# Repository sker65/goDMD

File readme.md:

# goDMD

Firmware for den pinguino micro zum bau einer goDmd Uhr.

Blog mit Anleitungen und vielen weiter führenden Hinweisen auf http://go-dmd.de/

# Setup der IDE

Als IDE kann Eclipse IDE genutzt werden. Siehe http://cogito-ergo-blog.de/blog/2015/02/25/eclipse-cdt-zur-pic-pic32-entwicklung-nutzen/

# Setup der Umgebung

Dieses Projekt nutzt einen chipKit core und einige Bibliotheken daraus. Um einen passende Core als libCore_api.a zum Linken zu haben, 
empfielt es sich dafür ebenfalls ein Eclipse CDT Projekt zu machen.
Auf dieses Projekt kann dann verwiesen werden.

## Libraries

Die Libraries die genutzt werden sind direkt aus dem Eclipse Workspace heraus verlinkt und 
zeigen auf die UECIDE Installation im home verzeichnis, wo der chipKit core Quellcode abgelegt ist.
Hier sind ggf. die Pfade in den Eclipse-Links anzupassen.

## IRremote Library
Die IR Remote Library wurde für den _Empfang_ an die PIC Umgebung angepasst und das Recorden
des IR Eingangs im Interrput angepasst.

Was nicht geht ist das Senden von IR Command. Die betreffen Stellen, die die PWM Signale 
erzeugen müssen noch von Arduino nach PIC portiert werden.

# SD Library
Diese Library ist eine projekt lokale Kopie der Lib aus dem ChipKIT core mit kleineren 
Anpassungen, damit sie aus dem pinguino micro ohne Probleme läuft.

Änderungen:
SD:
- seekCur eingefügt.

Sd2Card:
- setTranfersize to 8 bit
- setSpeed to 10000000UL (instead of 20000000UL) faster speed does not work

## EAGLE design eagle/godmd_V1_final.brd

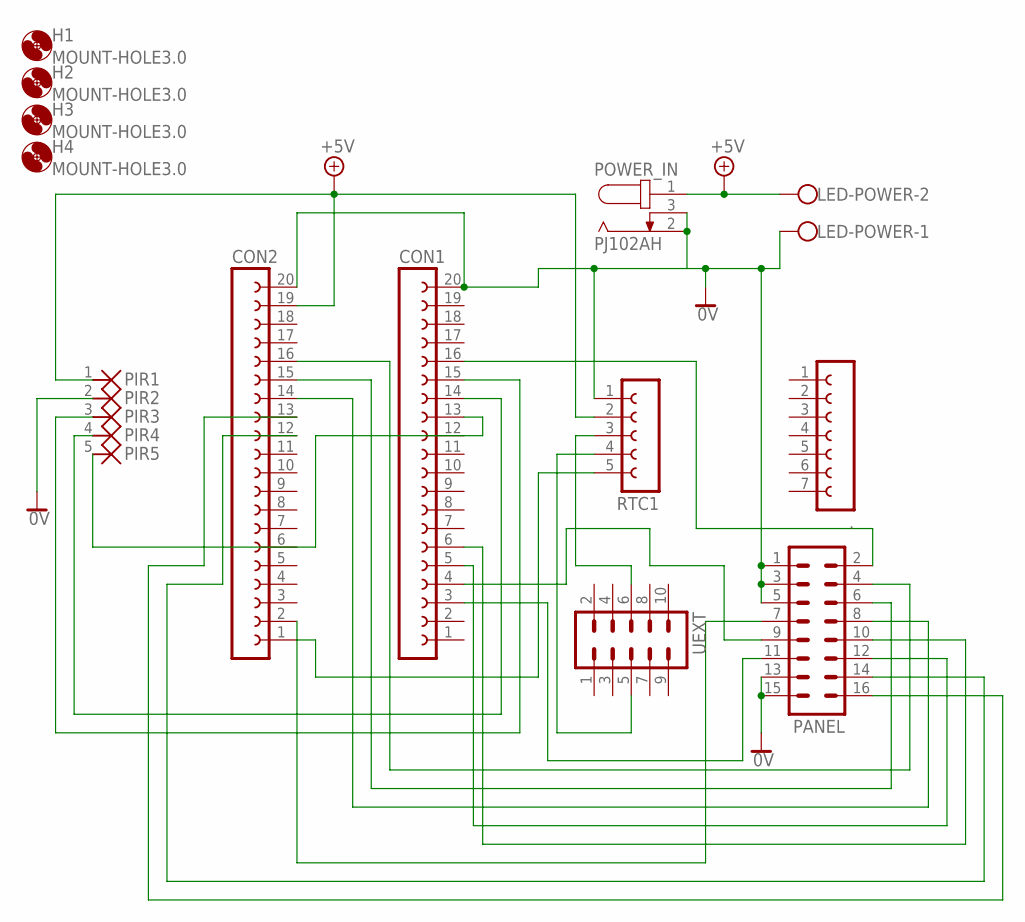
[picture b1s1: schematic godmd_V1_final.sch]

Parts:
.: FE07-1; FE07
CON1, CON2: FE20-1; FE20
H1, H2, H3, H4: MOUNT-HOLE3.0; 3,0
LED-POWER: W237-102
PANEL: MA08-2
PIR: PS25_5
POWER_IN: PJ102AH; PJ102
RTC1: FE05-1
UEXT: ML10

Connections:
0V: CON1.20, CON2.20, LED-POWER.1, PANEL.1, PANEL.3, PANEL.5, PANEL.13, PANEL.15, PIR.2, POWER_IN.2 (1), POWER_IN.3 (2), RTC1.1
+5V: CON2.19, LED-POWER.2, PIR.1, POWER_IN.1 (3), RTC1.2
A: CON1.16, PANEL.2
B: CON2.16, PANEL.4
C: CON2.15, PANEL.6
CLK: CON2.13, PANEL.16
D: CON2.14, PANEL.8
GD1: CON1.6, PANEL.10
GD2: CON1.5, PANEL.12
IRREC: CON1.14, PIR.4
LAT: CON2.12, PANEL.14
unnamed: RTC1.3, UEXT.6
unnamed: RTC1.4, UEXT.5
unnamed: CON2.1, RTC1.5
unnamed: CON2.2, PANEL.7
PIR-AUX: CON1.13, PIR.5
PIRDATA: CON1.15, PIR.3
RD1: CON1.4, PANEL.9
RD2: CON1.3, PANEL.11

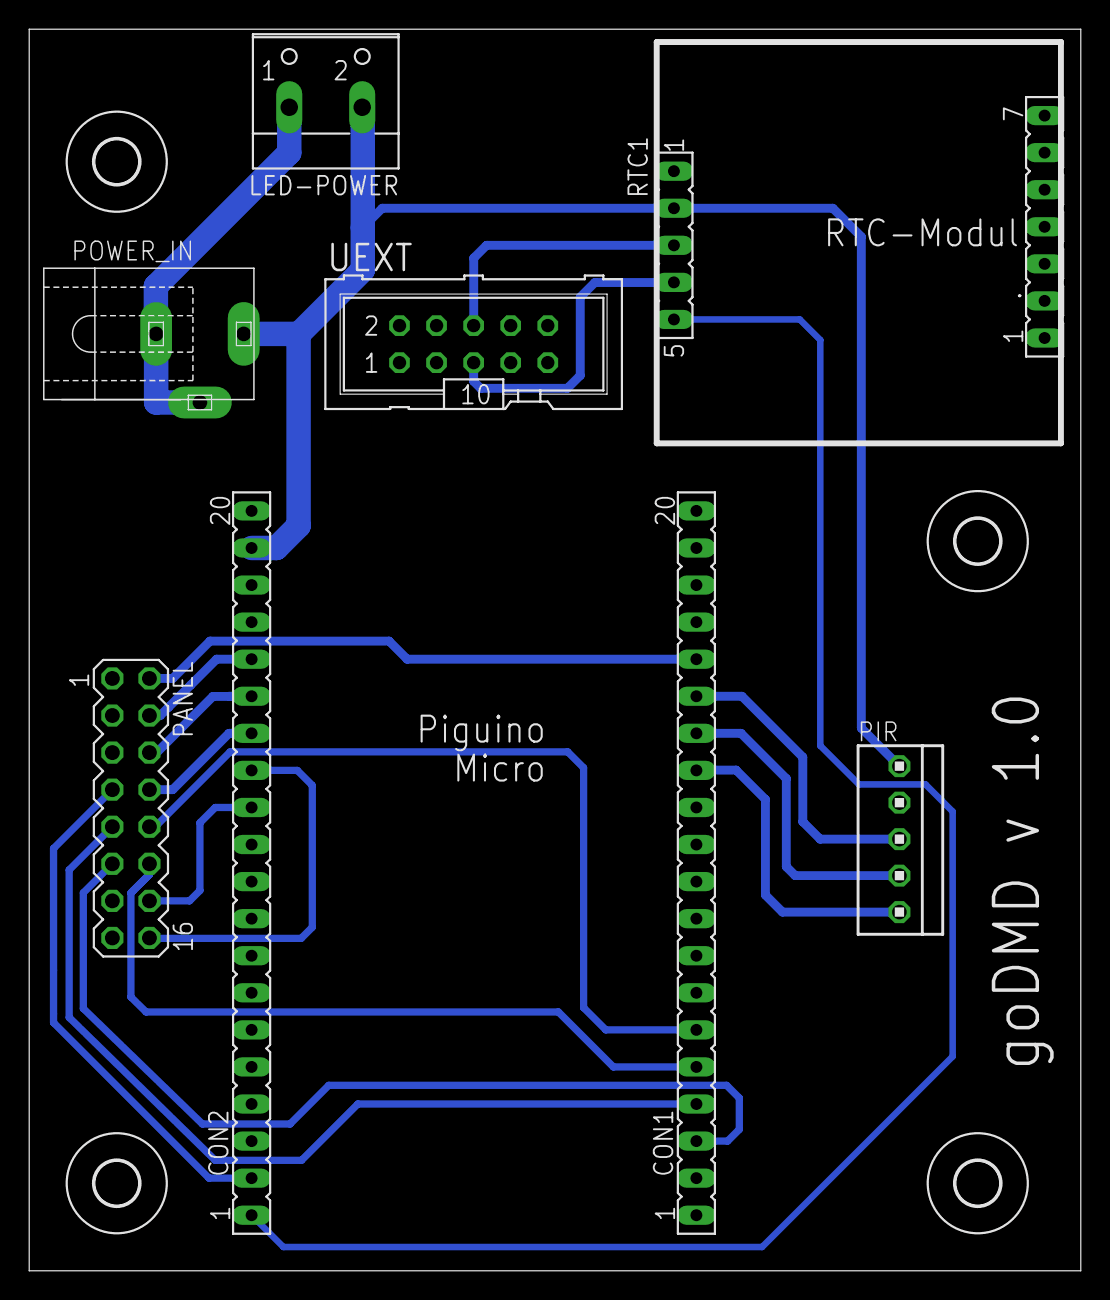
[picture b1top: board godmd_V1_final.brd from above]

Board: 2 copper layers, 72.1 x 85.1 mm, 13 parts (0 on the bottom side), 19 nets.

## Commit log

2015-02-27 first
2015-03-03 - switch to eclipse
2015-03-03 - use ptr not ref on rtc
2015-03-03 - use ptr to clock ref
2015-03-04 - added font loading from file - added temperature display
2015-03-04 - used for debug printf output via serial
2015-03-04 - used new DPRINTF macro for debug output
2015-03-04 - new debug macro for PRINTF - temp sensor linked with clock
2015-03-04 -old cfg from uecide
2015-03-04 - added eagle files
2015-03-05 - added small font
2015-03-05 - added dynamic font loading
2015-03-05 - debug start and test temp mode
2015-03-05 - removed some unused (arduino) stuff
2015-03-05 - merged old todo list
2015-03-05 - new version moved issues as real issues
2015-03-05 - switched on DEBUG
2015-03-05 - added eclipse settings
2015-03-05 - added build dirs to ignore
2015-03-05 - remove old files (ino, target hex file)
2015-03-05 - cleanup debug output, added some comments
2015-03-05 - doku setup umgebung
2015-03-05 - format
2015-03-05 - removed local copy of DSPI lib, used linked instead
2015-03-05 - changed and fixed font read / write
2015-03-05 - load options file just from setup
2015-03-05 - fixed debug output
2015-03-11 - added bitblt primitives
2015-03-11 - added fsk filter - added x,y offset for small clock
2015-03-11 - fixed cycling - added handling for small clock - added fsk filter (not working until now)
2015-03-11 - added big / small font handling
2015-03-11 - added big / small font handling - removed hard coded font image, instead load font from file - use bitblt to render font into buffer
2015-03-11 - make buffers itself volatile
2015-03-11 - changed bit buffer row pixel placement to linear
2015-03-11 - added fsk filter
2015-03-11 - added temp mode for showing temperatur (sensor not working at the moment)
2015-03-11 - next
2015-03-11 - when skipping frames just read len of buf each time
2015-03-13 - new config mene entries
2015-03-16 - clock now supports non blinking tick / 12 hour format
2015-03-16 - support for clock modes
2015-03-16 - support for random order of animations
2015-03-16 - menu item for ani order
2015-03-16 - fixed time offset bug - fixed check temperatur
2015-03-16 - support for random order
2015-03-27 - readNextFrame returns actual delay
2015-03-27 - support mask planes
2015-03-27 - no msg
2015-03-27 - clear clock
2015-03-27 - small no sec
2015-03-27 - reverted handling for color
2015-03-27 - support double buffer
2015-03-27 - revert
2015-03-27 - use pir handler
2015-03-27 - foo
2015-04-30 - new doc
2015-05-02 - externalize ir-codes for final controller
2015-05-02 - just whitespace
2015-05-02 - use externalized logical codes
2015-05-02 - fixed panel delete (just delete Animations buffer, not clock)
2015-05-02 - handling masking of clock digits for background and transistions
2015-05-02 - handle transitions
2015-05-02 - first version of selftest
2015-05-05 - create two different long presses
2015-05-05 - not boolean if long press, but int 0,1,2
2015-05-05 - selftest on failure - try yellow led
2015-05-05 - few optimazations, scan order
2015-05-05 - scan order
2015-05-05 - use three state button
2015-05-06 - support for prop fonts
2015-05-06 - font config
2015-05-06 - support for multi fonts
2015-05-06 - minor order when init - multi font support
2015-05-08 - lower case
2015-05-08 - add positive led logik 0 = off, 1 = on
2015-05-08 - externalize version string
2015-05-08 - introduced new version.h - inc. version to rc2
2015-05-08 - new test mode - color cycling
2015-05-08 - LEDS active high - birghtness controll
2015-05-08 - brightness menu
2015-05-08 - new version rc3
2015-05-08 - clock change only when ani finished
2015-05-09 - selftest
2015-05-09 - brightness save fixes
2015-05-09 - added actual state for test
2015-05-09 - v1.01
2015-05-09 - added serial handler for time adjust
2015-05-09 - bugfix pir pinmode
2015-05-16 - remove flickering in self test
2015-08-02 - support for transition name in ANI
2015-08-02 - system clock define to 60Mhz
2015-08-02 - minor refactoring just to not set mode if nothing changed
2015-08-02 - adjust menu to support options for date / temp duration
2015-08-02 - bump version to 1.02
2015-08-02 - changed transition logic
2015-08-02 - added options doku fiel
2015-08-02 - option for led indicator
2015-08-02 - support for hold incl. transitions
2015-08-02 - support for masking digits
2015-08-02 - bugfix clock on for date temp
2015-08-02 - support for clock mask when front
2015-08-02 - 1.03
2015-08-03 - adjusted ir receiver interrupt timer to 60Mhz sysclock
2015-08-03 - new codes because new timing
2015-08-03 - pir hold time adjustable
2015-08-03 - version
2015-08-03 - pir hold time
2015-08-05 - bugfix no ani left
2015-08-07 fixed temp staying while ani
2015-08-07 - added temp offset - display of aniname
2015-08-07 - temp offset - bug #27 temp displayed "behind" ani
2015-08-07 - display aniname
2015-08-07 - fix ir codes with different receivers
2015-08-07 - show name support - temp offset
2015-08-09 - first version of time util that has summertime support
2015-08-12 - fixes #27, animation transition with date or temp
2015-08-13 - new util class for daylight saving, should be included in classes already used
2015-08-13 - fixes #27 - introduced new macro for save compare with overflow
2015-08-13 - introduced macro util
2015-08-13 - first version of node mcu intregration
2015-08-13 - added net config
2015-08-13 - save cmp
2015-08-13 - 1.07
2015-08-13 - use common version of codes
2015-08-13 - version tool script
2015-08-15 - improved node adapter
2015-08-18 -remove TODO comments
2015-08-18 - callback handler für ntp
2015-08-18 - adjust util just todo dls
2015-08-18 - another rc with bugfixes
2015-08-18 - integrated ntp callback handler
2015-08-20 - adjust timing, 100us sample rate
2015-08-20 - support two types of debug macro
2015-08-20 - add debug message
2015-08-20 - added second macro for file / func output
2015-08-20 - use just the right ones
2015-08-20 - support for new debug macro
2015-08-20 - first functional
2015-08-20 - integrate node and request ntp once after switch on
2015-08-20 - new debug macros
2015-08-20 - new debug macro
2015-08-20 - async sending of cmds
2015-08-21 -fix getip
2015-08-21 - status fuer wifi
2015-08-24 Fixes #42 - just a typo in hex code constant
2015-08-24 Fixes #41 - when in selftest, one can transparently use Serial to access the ESP
2015-08-24 - added debug output to better see random order
2015-08-24 - fixed random play order bug - refactored resetting of anis
2015-08-25 new cb handler for display
2015-08-25 adjust menu handling to bg processing
2015-08-25 - adjust selftest with getip
2015-08-25 - added heap request, background cmd disable
2015-08-26 - version - bugfix in menu cycle when in net menu - fixes #46
2015-08-26 - limit status to known values
2015-08-27 support pre-set of wifi settings on SD file
2015-09-08 Proof of concept code for wireless upload
2015-09-09 Wifi Upload
2015-09-09 - added lua code
2015-09-21 - added compression algo - added compressed tftp.lua
2015-10-05 fixes #32 , overflow of millis
2015-10-05 - fixes stuck in net menu
2015-10-25 -added debug output
2015-10-25 -fixed SAVECMP using signed subtract
2015-10-25 - use unsigned long for nextAniUpdate
2015-10-25 - fixed daylight saving bug using 2000 offset
2016-02-18 - added getter for unixtime
2016-02-18 - automatic dst check / switch
2016-02-18 perpare node udp server
2016-03-29 - bugfix for dst check
2016-03-29 - version 1.10
2016-05-07 experimental support for DHT
